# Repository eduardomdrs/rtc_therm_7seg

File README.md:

# rtc_therm_7seg
An arduino based project combining a RTC, a thermometer and a 4-digit 7 segment display.

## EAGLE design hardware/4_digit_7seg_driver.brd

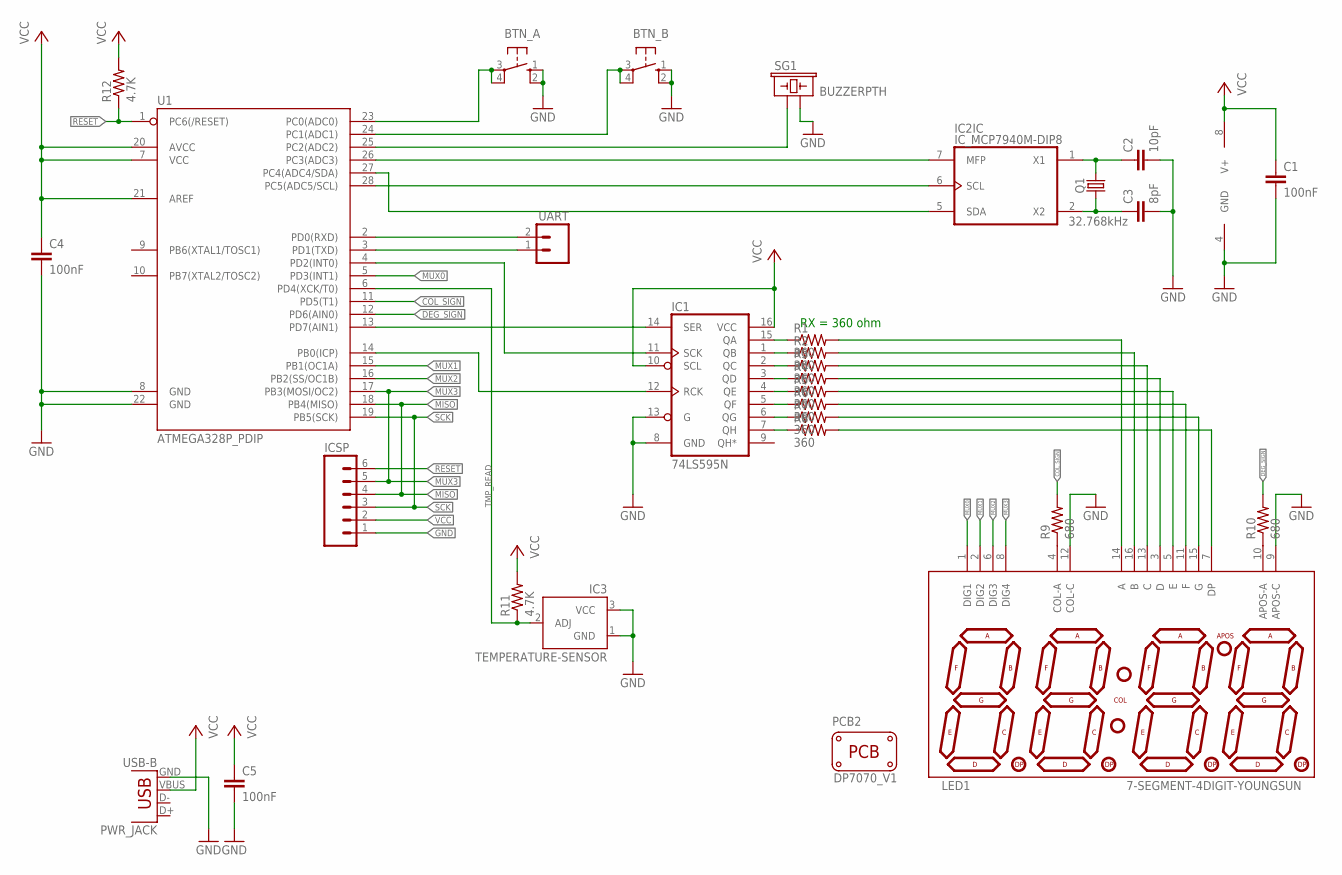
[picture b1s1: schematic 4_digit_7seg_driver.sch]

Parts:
BTN_A: 40-XX; B3F-40XX
BTN_B: 40-XX; B3F-40XX
C1, C4, C5: 100nF; CAP-PTH-5MM
C2: 10pF; CAP-PTH-SMALL
C3: 8pF; CAP-PTH-SMALL
IC1: 74LS595N; DIL16
IC2: IC_MCP7940M-DIP8; DIP8
IC3: TEMPERATURE-SENSOR; TO-92
ICSP: M06SILK_FEMALE_PTH; 1X06
LED1: 7-SEGMENT-4DIGIT-YOUNGSUN
PCB2: PCB_DP_SQUARE-7X7; DP7070_V1
PWR_JACK: USB-B; USB-B-PTH
Q1: 32.768kHz; TC26V
R1, R2, R3, R4, R5, R6, R7, R8: 360; AXIAL-0.1
R9, R10: 680; AXIAL-0.1
R11, R12: 4.7K; AXIAL-0.1
SG1: BUZZERPTH; BUZZER-12MM
U1: ATMEGA328P_PDIP; DIL28-3
UART: M02PTH; 1X02

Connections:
A: LED1.14 (A), R1.P$2 (2)
B: LED1.16 (B), R2.P$2 (2)
BUTTON_A: BTN_A.3, BTN_A.4 (P1), U1.23 (PC0(ADC0))
BUTTON_B: BTN_B.3, BTN_B.4 (P1), U1.24 (PC1(ADC1))
C: LED1.13 (C), R3.P$2 (2)
COL_SIGN: R9.P$2 (2), U1.11 (PD5(T1))
D: LED1.3 (D), R4.P$2 (2)
DEG_SIGN: R10.P$2 (2), U1.12 (PD6(AIN0))
DP: LED1.7 (DP), R8.P$2 (2)
E: LED1.5 (E), R5.P$2 (2)
F: LED1.11 (F), R6.P$2 (2)
G: LED1.15 (G), R7.P$2 (2)
GND: BTN_A.1 (S), BTN_A.2 (S1), BTN_B.1 (S), BTN_B.2 (S1), C1.2, C2.2, C3.2, C4.2, C5.2, IC1.8 (GND), IC1.13 (G), IC2.4 (GND), IC3.1 (GND), IC3.3 (VCC), ICSP.1, LED1.9 (APOS-C), LED1.12 (COL-C), PWR_JACK.GND, SG1.- (2), U1.8 (GND), U1.22 (GND)
MISO: ICSP.4, U1.18 (PB4(MISO))
MUX0: LED1.1 (DIG1), U1.5 (PD3(INT1))
MUX1: LED1.2 (DIG2), U1.15 (PB1(OC1A))
MUX2: LED1.6 (DIG3), U1.16 (PB2(SS/OC1B))
MUX3: ICSP.5, LED1.8 (DIG4), U1.17 (PB3(MOSI/OC2))
unnamed: IC1.15 (QA), R1.P$1 (1)
unnamed: IC1.1 (QB), R2.P$1 (1)
unnamed: IC1.2 (QC), R3.P$1 (1)
unnamed: IC1.3 (QD), R4.P$1 (1)
unnamed: IC1.4 (QE), R5.P$1 (1)
unnamed: IC1.5 (QF), R6.P$1 (1)
unnamed: IC1.6 (QG), R7.P$1 (1)
unnamed: IC1.7 (QH), R8.P$1 (1)
unnamed: LED1.4 (COL-A), R9.P$1 (1)
unnamed: IC2.6 (SCL), U1.28 (PC5(ADC5/SCL))
unnamed: IC2.5 (SDA), U1.27 (PC4(ADC4/SDA))
unnamed: IC2.7 (MFP), U1.26 (PC3(ADC3))
unnamed: SG1.+ (1), U1.25 (PC2(ADC2))
unnamed: C2.1, IC2.1 (X1), Q1.2
unnamed: LED1.10 (APOS-A), R10.P$1 (1)
unnamed: C3.1, IC2.2 (X2), Q1.1
RESET: ICSP.6, R12.P$1 (1), U1.1 (PC6(/RESET))
SCK: ICSP.3, U1.19 (PB5(SCK))
S_CLK: IC1.11 (SCK), U1.4 (PD2(INT0))
S_DATA: IC1.14 (SER), U1.13 (PD7(AIN1))
S_LATCH: IC1.12 (RCK), U1.14 (PB0(ICP))
TMP_READ: IC3.2 (ADJ), R11.P$1 (1), U1.6 (PD4(XCK/T0))
UART_RX: U1.2 (PD0(RXD)), UART.2
UART_TX: U1.3 (PD1(TXD)), UART.1
VCC: C1.1, C4.1, C5.1, IC1.10 (SCL), IC1.16 (VCC), IC2.8 (V+), ICSP.2, PWR_JACK.VBUS, R11.P$2 (2), R12.P$2 (2), U1.7 (VCC), U1.20 (AVCC), U1.21 (AREF)

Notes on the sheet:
RX = 360 ohm

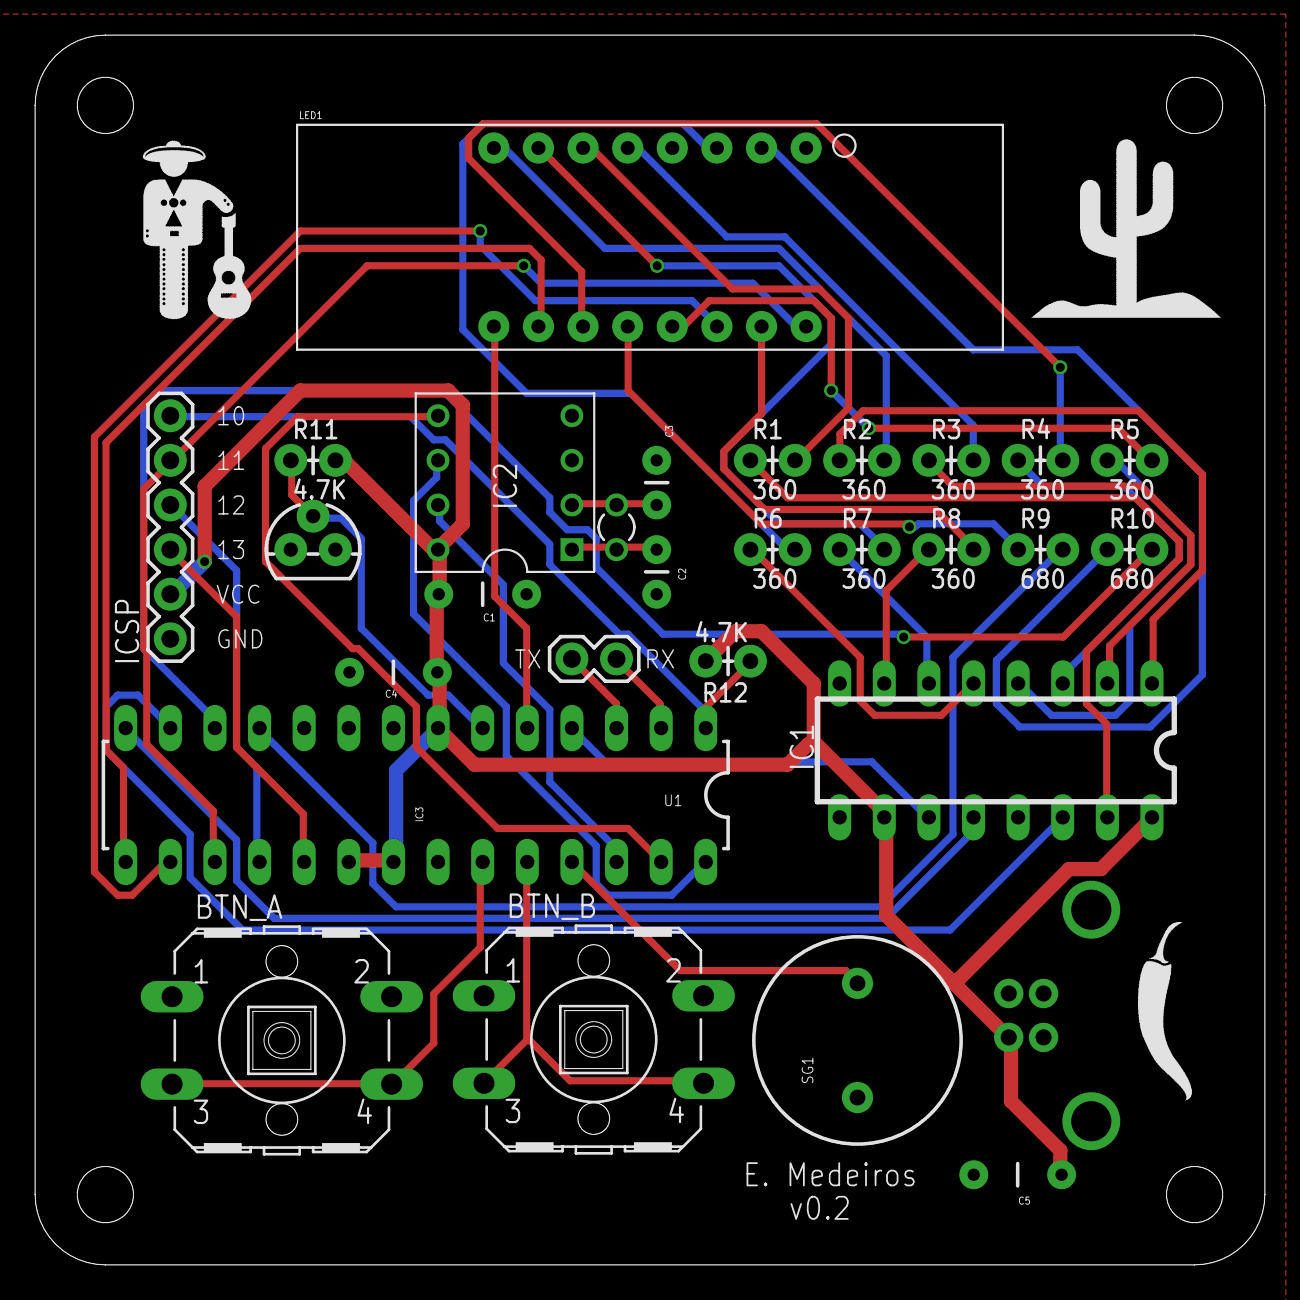
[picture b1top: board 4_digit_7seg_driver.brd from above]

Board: 2 copper layers, 70.0 x 70.0 mm, 30 parts (1 on the bottom side), 43 nets.

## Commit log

2015-07-25 adding initial files for 7seg display driver
2015-07-30 updates in SevenSegController, first version of sketch
2015-07-30 removing old display_test sketch
2015-07-30 changes in display controller
2015-08-20 changes to support pwm pins instead of digital.
2015-08-20 removing unnecessary files
2015-09-04 adding makefile for non-ide development
2015-09-04 change order of functions to appease gcc
2015-09-19 changes to support playing alarm song, removing pwm muxing, slowing update frequency, removing interrupt when disabling display
2015-09-19 adding functionality for short display messages, changing digit representation from byte to char
2015-09-19 adding functionality to edit, enable and disable audible alarm
2015-09-19 adding functionality to read and write alarm setting to sram
2015-09-19 the user interface for setting and enabling/disabling alarms is done
2015-09-22 added control functions to operate RTC alarm functions
2015-09-22 updating code to deal with ERROR states, adding debug serial messages for alarm status
2015-09-22 adding states to treat alarms
2015-09-22 adding E letter
2015-09-24 adding temtative alarm implementation
2015-09-24 fixing initialization order, still must test error mode code
2015-09-24 Improved serial port debug messages
2015-09-25 change alarm implementation
2015-12-08 many changes in the main script, fixed alarm functionality and reimplemented alarmAlert playing, enabling it to be stopped
2016-01-24 adding automatic alarm re-trigger. Also allowing alarm and time edit transition from SHOW_TEMP state
2016-01-31 fixing the re-triggering mechanism, also fixing identation
2016-08-05 updating alarm structure, adding .h for top level file
2016-08-05 renaming files
2016-08-06 adding pcb design files
2016-08-06 standardizing identation tabs/4spaces
2016-08-06 identation
2016-08-06 adding schem. pdf
2016-08-06 adding FSM diagram
2016-08-06 adding png version
2016-08-06 fixing alarm behavior

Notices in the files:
parts and their libraries:
SparkFun-Passives: Licensing: Creative Commons ShareAlike 4.0 International - https://creativecommons.org/licenses/by-sa/4.0
